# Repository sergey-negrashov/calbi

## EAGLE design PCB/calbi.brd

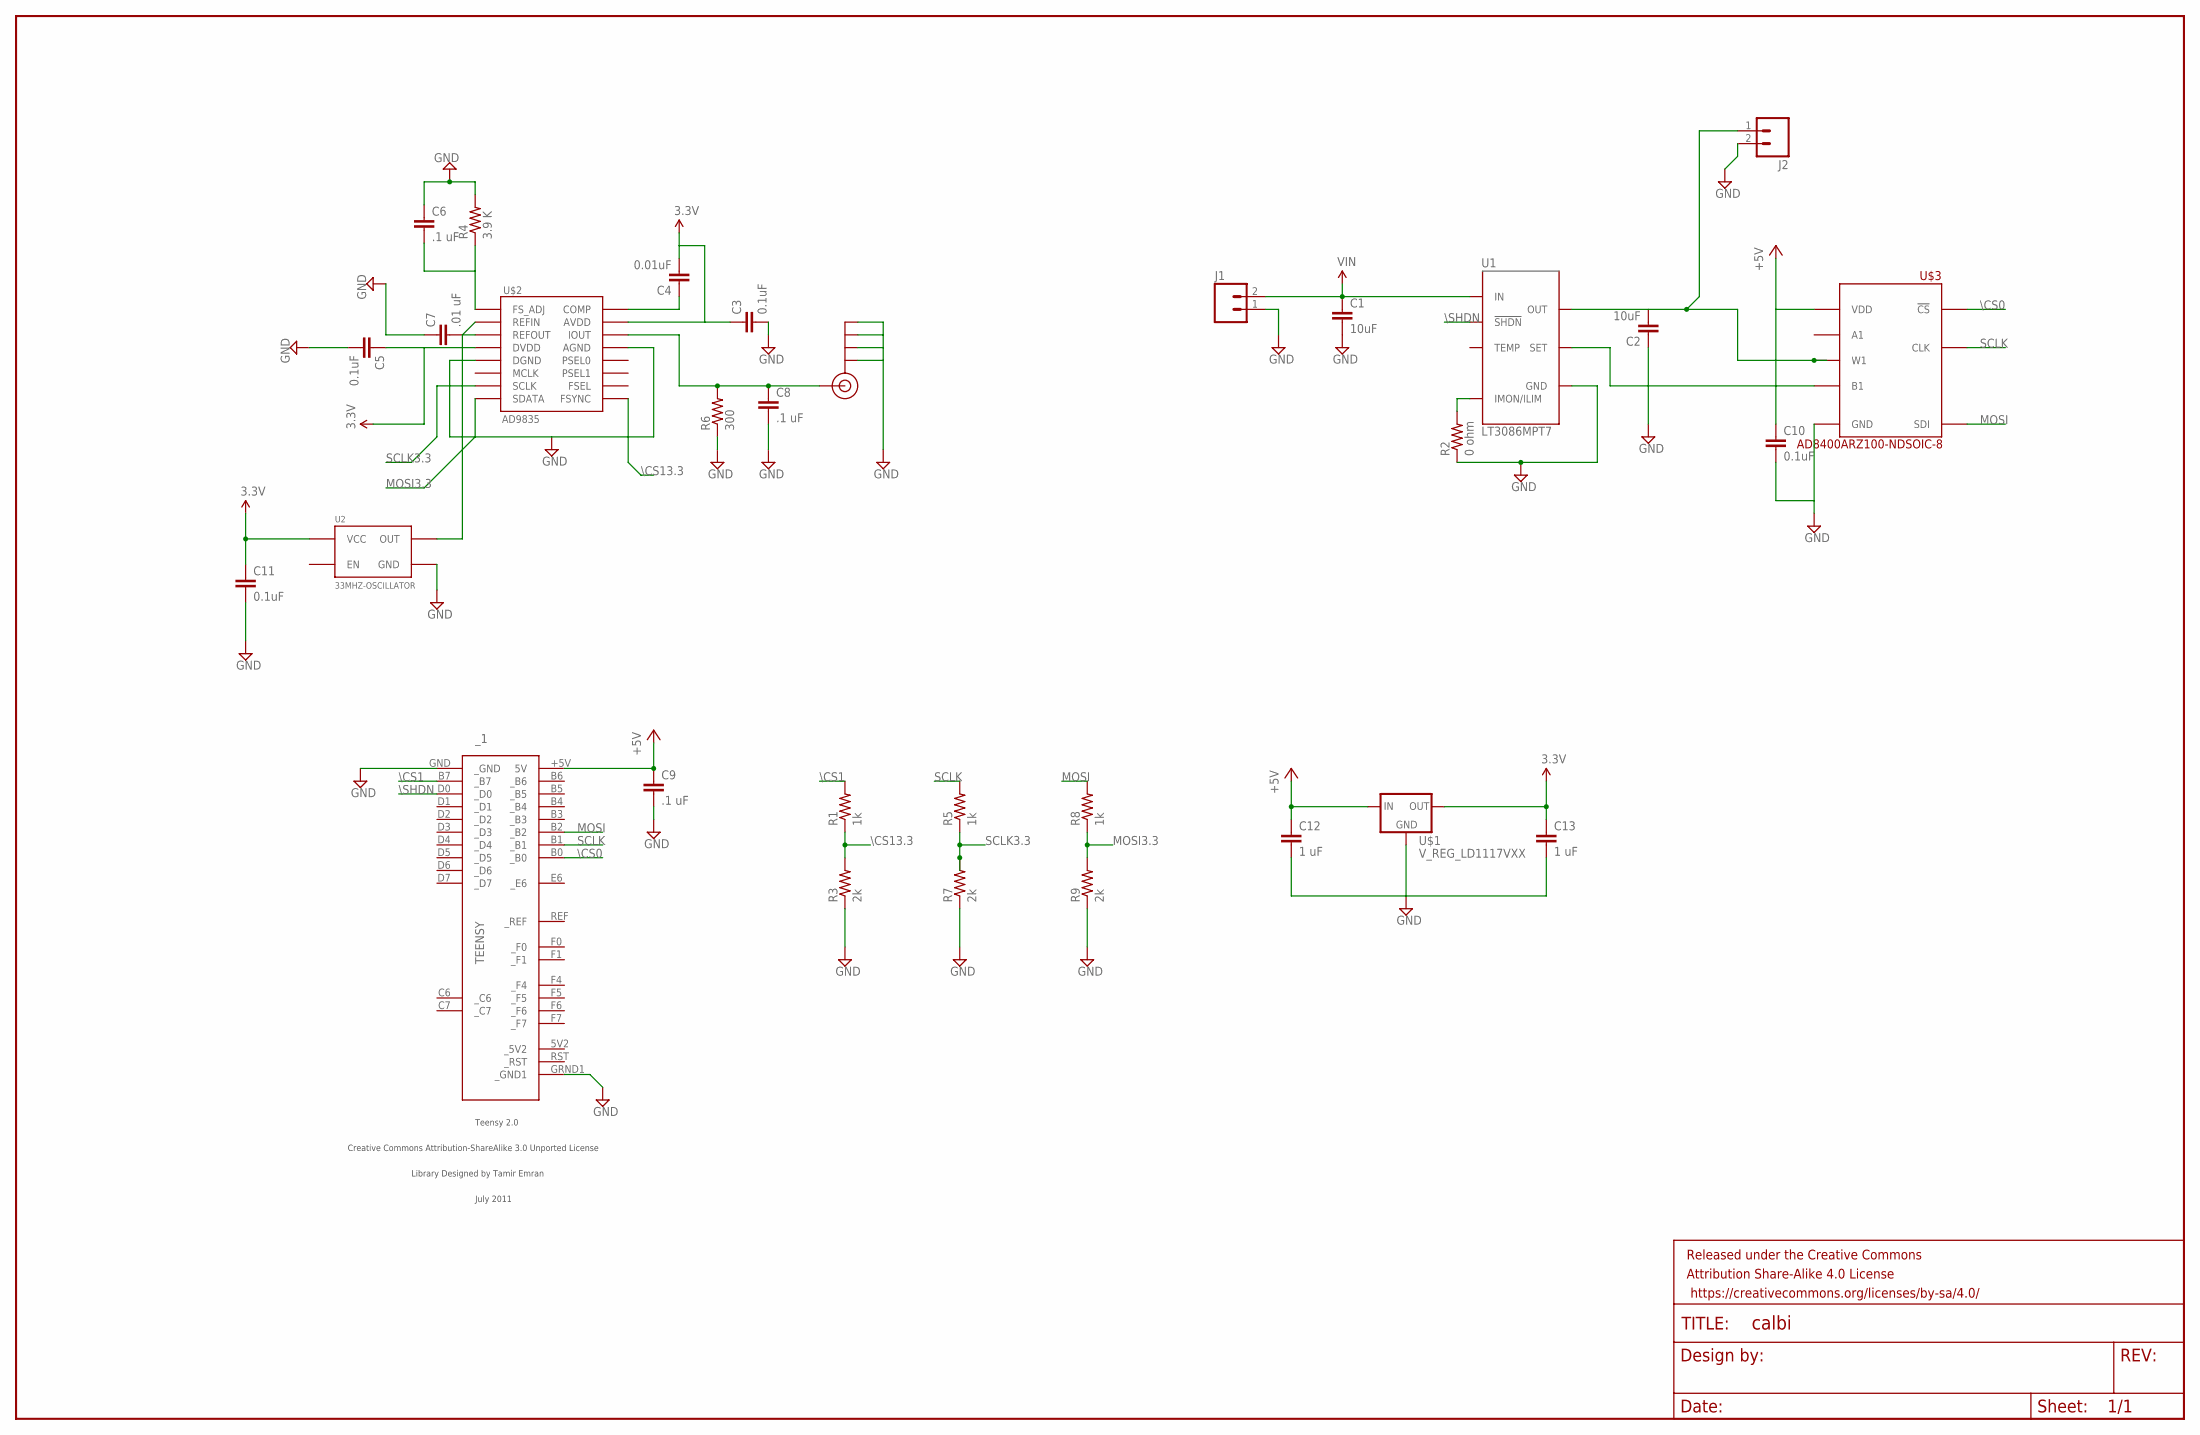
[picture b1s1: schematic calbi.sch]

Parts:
C1, C2: 10uF; 0603-CAP
C3, C5, C10, C11: 0.1uF; 0603-CAP
C4: 0.01uF; 0603-CAP
C6, C8, C9: .1 uF; 0603-CAP
C7: .01 uF; 0603-CAP
C12, C13: 1 uF; 0603-CAP
FRAME1: FRAME-LEDGER; CREATIVE_COMMONS
J1, J2: M023.5MM; SCREWTERMINAL-3.5MM-2
J$1: SMA_EDGE; SMA-EDGE
R1, R5, R8: 1k; 0603-RES
R2: 0 ohm; 0603-RES
R3, R7, R9: 2k; 0603-RES
R4: 3.9 K; 0603-RES
R6: 300; 0603-RES
U1: LT3086MPT7; TO220-7
U2: 33MHZ-OSCILLATOR; CRYSTAL-OSC-SMD-5X3.2
U$1: V_REG_LD1117VXX; 78XXL
U$2: AD9835; TSSOP16
U$3: AD8400ARZ100-NDSOIC-8; SO08
_1: TEENSY

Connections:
3.3V: C3.1, C4.2, C5.1, C11.1, C13.1, U2.4 (VCC), U$1.GND (OUT), U$2.4 (DVDD), U$2.15 (AVDD)
+5V: C9.1, C10.1, C12.1, U$1.OUT (IN), U$3.6 (VDD), _1.+5V (5V)
GND: C1.2, C2.1, C3.2, C5.2, C6.1, C7.1, C8.2, C9.2, C10.2, C11.2, C12.2, C13.2, J1.1, J2.2, J$1.GND@0 (GND), J$1.GND@1 (GND), J$1.GND@2 (GND), J$1.GND@3 (GND), R2.1, R3.1, R4.2, R6.1, R7.1, R9.1, U1.4 (GND), U2.2 (GND), U$1.IN (GND), U$2.5 (DGND), U$2.13 (AGND), U$3.2 (GND), _1.GND (_GND), _1.GRND1 (_GND1)
MOSI: R8.2, U$3.4 (SDI), _1.B2 (_B2)
MOSI3.3: R8.1, R9.2, U$2.8 (SDATA)
unnamed: C7.2, U$2.3 (REFOUT)
unnamed: R2.2, U1.1 (IMON/ILIM)
unnamed: C8.1, J$1.SIG (SIGNAL), R6.2, U$2.14 (IOUT)
unnamed: C4.1, U$2.16 (COMP)
unnamed: C2.2, J2.1, U1.3 (OUT), U$3.7 (W1)
unnamed: U2.3 (OUT), U$2.2 (REFIN)
unnamed: C6.2, R4.1, U$2.1 (FS_ADJ)
unnamed: C1.1, J1.2, U1.5 (IN)
unnamed: U1.2 (SET), U$3.1 (B1)
SCLK: R5.2, U$3.5 (CLK), _1.B1 (_B1)
SCLK3.3: R5.1, R7.2, U$2.7 (SCLK)
\CS0: U$3.3 (!CS), _1.B0 (_B0)
\CS1: R1.2, _1.B7 (_B7)
\CS13.3: R1.1, R3.2, U$2.9 (FSYNC)
\SHDN: U1.6 (!SHDN), _1.D0 (_D0)

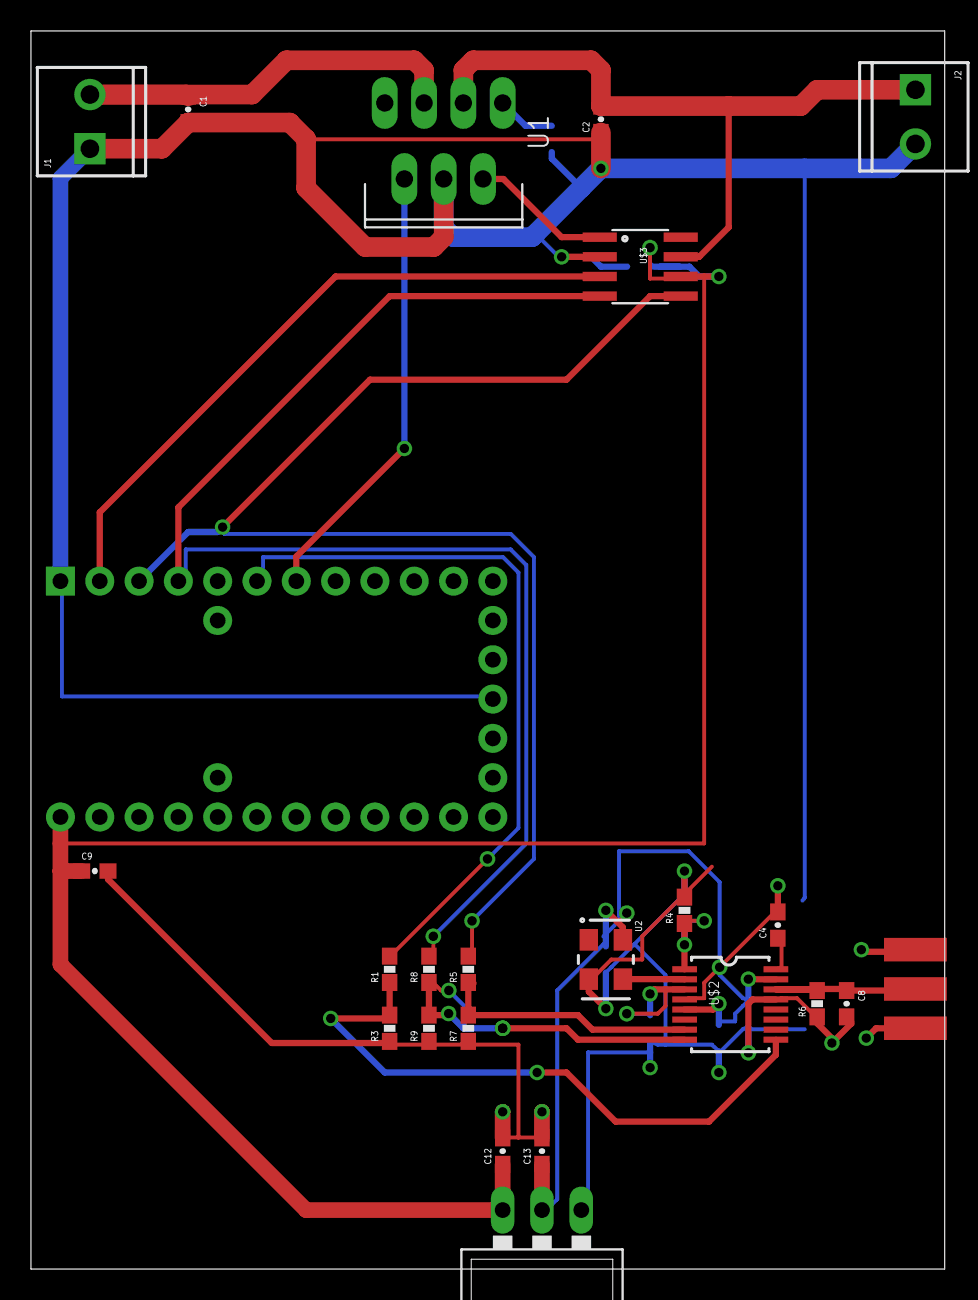
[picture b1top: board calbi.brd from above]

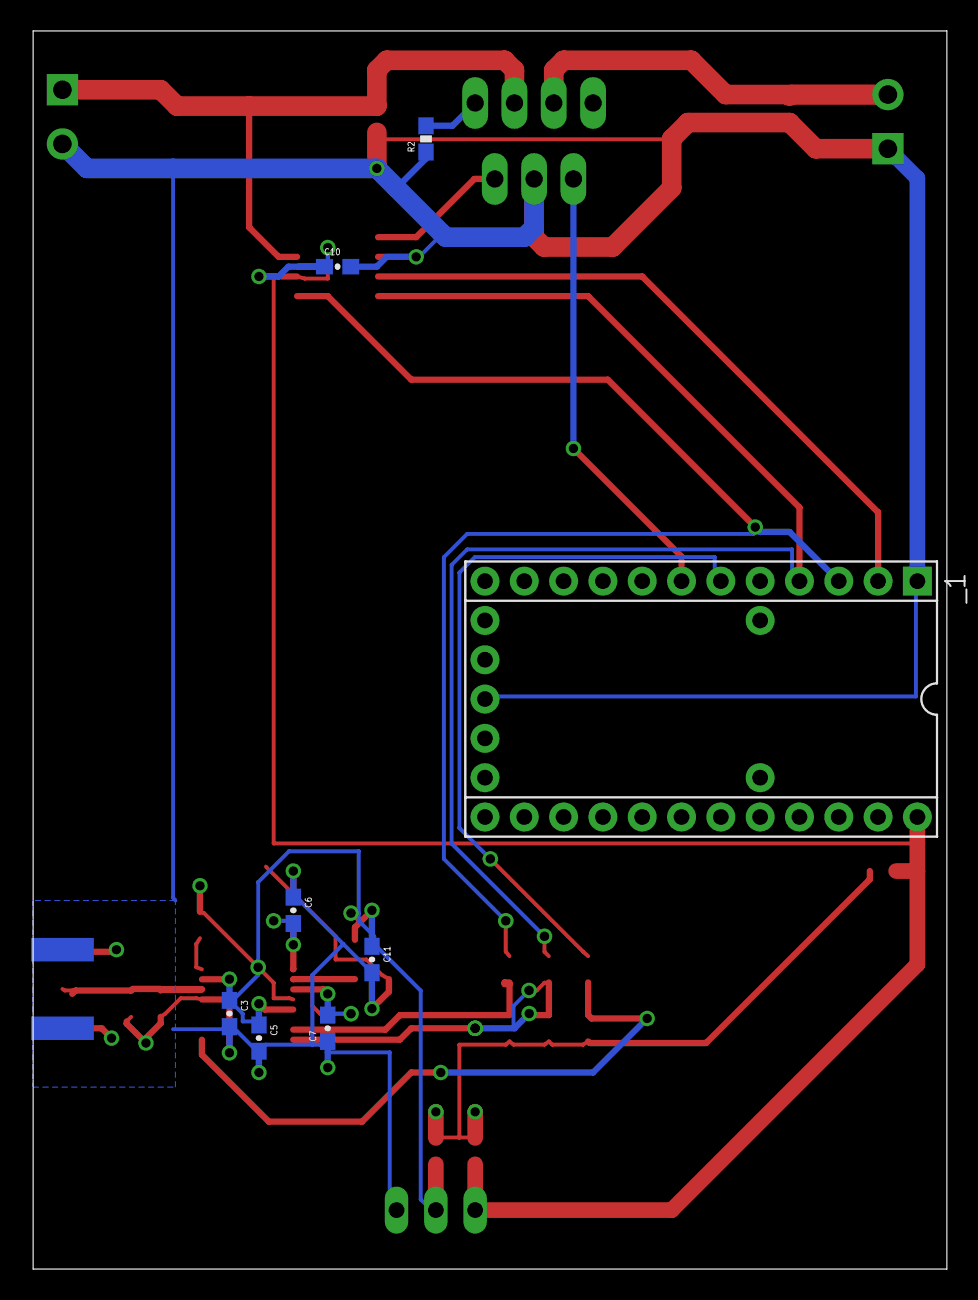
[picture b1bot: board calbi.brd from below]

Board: 2 copper layers, 59.0 x 80.0 mm, 32 parts (8 on the bottom side), 20 nets.

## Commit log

2016-04-16 added couple parts
2016-04-16 AD9835
2016-04-16 Initial pcb import
2016-04-20 added ad8400 footprint
2016-04-20 added teensy 3.0
2016-04-21 Schematic for AD9835 finished
2016-04-22 Finished schematic for power supply
2016-04-26 Finished the schematic
2016-04-26 Fixed a couple of errors in the schematic. Layed out power. Going to meet on Wednesday at 3:30 to do the RF layout
2016-04-28 Commiting changes from Wednesday
2016-04-30 FInished up a few things. Set up the cam.

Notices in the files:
parts and their libraries:
SparkFun-Capacitors: Licensing: Creative Commons ShareAlike 4.0 International - https://creativecommons.org/licenses/by-sa/4.0
SparkFun-Aesthetics: Released under the Creative Commons Attribution Share-Alike 4.0 License
SparkFun-Aesthetics: https://creativecommons.org/licenses/by-sa/4.0
